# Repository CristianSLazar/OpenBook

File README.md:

# Hardware Functionality

The OpenBook E-Reader is designed with a focus on simplicity, sustainability, and open-source flexibility. Below is a detailed breakdown of its hardware components, interfaces, communication specifications, processes, and power consumption considerations.

## Block Diagram

## Bill of Materials

| Qty | Value | Device | Package | Parts | PURCHASE-URL | DATASHEET-URL |
| --- | ----- | ------ | ------- | ----- | ------------ | ------------- |
| 1 |  | ADAFRUIT_LEDCHIP-LED0603 | 0603 | CHG_LED | https://www.digikey.com/en/products/detail/w%C3%BCrth-elektronik/150060RS75000/4489901 | https://www.we-online.com/components/products/datasheet/150060RS75000.pdf |
| 1 | 0.1uF/50V | ESP32_WROVER_EAGLE-LTSPICE_C0402 | 0402 | EPD_C3 | https://www.digikey.com/en/products/detail/samsung-electro-mechanics/CL05B104KB5NNNC/11696318 | https://weblib.samsungsem.com/mlcc/mlcc-ec-data-sheet.do?partNumber=CL05B104KB5NNN |
| 1 | 0.47 | ESP32_WROVER_EAGLE-LTSPICE_RR0402 | 0402 | R3 | https://www.digikey.com/en/products/detail/panasonic-electronic-components/ERJ-2BQJR47X/5647384 | https://industrial.panasonic.com/cdbs/www-data/pdf/RDN0000/AOA0000C313.pdf |
| 1 | 100K | ESP32_WROVER_EAGLE-LTSPICE_RR0402 | 0402 | R_PWRUSB | https://www.digikey.com/en/products/detail/panasonic-electronic-components/ERJ-2RKF1003X/192081 | https://industrial.panasonic.com/cdbs/www-data/pdf/RDA0000/AOA0000C304.pdf |
| 8 | 100nF | ESP32_WROVER_EAGLE-LTSPICE_C0402 | 0402 | C1, C2, C3_USB, C5, C7, C8, C9, C_DELAY | https://www.digikey.com/en/products/detail/samsung-electro-mechanics/CL05B104KP5NNNC/3886660 | https://mm.digikey.com/Volume0/opasdata/d220001/medias/docus/609/CL05B104KP5NNNC_Spec.pdf |
| 1 | 100uF | RCL_CPOL-EUCT3528 | 3528 | C_TANT | https://ro.mouser.com/ProductDetail/KEMET/T491B107M006AT?qs=U312oeP%2FpiHOgyk6KO2m0g%3D%3D | https://ro.mouser.com/datasheet/2/447/KEM_T2005_T491-3316937.pdf
| 16 | 10K | ESP32_WROVER_EAGLE-LTSPICE_RR0402 | 0402 | R1, R1_PINH1, R1_PINH2, R2-PINH1, R2_PINH2, R4, R5, R6, R7, R8, R9, R10, R_BOOT, R_CHANGE, R_CL1, R_RESET | https://www.digikey.com/en/products/detail/panasonic-electronic-components/ERJ-2RKF1002X/192073 | https://industrial.panasonic.com/cdbs/www-data/pdf/RDA0000/AOA0000C304.pdf |
| 1 | 10uF | ESP32_WROVER_EAGLE-LTSPICE_C0402 | 0402 | C6 | https://www.digikey.com/en/products/detail/samsung-electro-mechanics/CL05A106MP5NUNC/3887108 | https://mm.digikey.com/Volume0/opasdata/d220001/medias/docus/2614/CL05A106MP5NUNC_Spec.pdf |
| 1 | 112A-TAAR-R03_ATTEND | 112A-TAAR-R03_ATTEND |  | J4 | https://www.digikey.ro/en/products/detail/attend-technology/112A-TAAR-R03/17633923 | https://www.attend.com.tw/data/download/file/112A-TAAR-R03_Spec.pdf |
| 1 | 15 | ESP32_WROVER_EAGLE-LTSPICE_RR0402 | 0402 | R_CAPACITOR | https://www.digikey.com/en/products/detail/panasonic-electronic-components/ERJ-2RKF15R0X/192142 | https://industrial.panasonic.com/cdbs/www-data/pdf/RDA0000/AOA0000C304.pdf |
| 1 | 1uF | ESP32_WROVER_EAGLE-LTSPICE_C0402 | 0402 | C4 | https://www.digikey.com/en/products/detail/samsung-electro-mechanics/CL05A105KO5NNNC/3886725 | https://mm.digikey.com/Volume0/opasdata/d220001/medias/docus/609/CL05A105KO5NNNC_Spec_5-2-19.pdf |
| 9 | 1uF/50V | ESP32_WROVER_EAGLE-LTSPICE_C0402 | 0402 | EPD_C1, EPD_C2, EPD_C4, EPD_C5, EPD_C6, EPD_C7, EPD_C8, EPD_C9, EPD_C10 | https://www.digikey.com/en/products/detail/murata-electronics/GRM155R61H105KE05D/13531808 | https://search.murata.co.jp/Ceramy/image/img/A01X/G101/ENG/GRM155R61H105KE05-01A.pdf |
| 1 | 2.2 | ESP32_WROVER_EAGLE-LTSPICE_RR0402 | 0402 | R2 | https://www.digikey.com/en/products/detail/panasonic-electronic-components/ERJ-2GEJ2R2X/282078 | https://api.pim.na.industrial.panasonic.com/file_stream/main/fileversion/1242 |
| 1 | 200 | ESP32_WROVER_EAGLE-LTSPICE_RR0402 | 0402 | R1_BAT | https://www.digikey.com/en/products/detail/panasonic-electronic-components/ERJ-2RKF2000X/192215 | https://industrial.panasonic.com/cdbs/www-data/pdf/RDA0000/AOA0000C304.pdf |
| 2 | 20V/4.2A/52mO/1.4W | ESP32_WROVER_SPARKFUN-DISCRETESEMI_MOSFET_PCH-DMG2305UX-7 |  | Q1, Q2 | https://www.digikey.ro/en/products/detail/diodes-incorporated/DMG2305UX-7/4340667 | https://www.diodes.com/assets/Datasheets/DMG2305UX.pdf |
| 1 | 2K | ESP32_WROVER_EAGLE-LTSPICE_RR0402 | 0402 | R2_BAT | https://www.digikey.com/en/products/detail/panasonic-electronic-components/ERJ-2RKF2001X/192194 | https://industrial.panasonic.com/cdbs/www-data/pdf/RDA0000/AOA0000C304.pdf |
| 5 | 4.7uF | ESP32_WROVER_EAGLE-LTSPICE_C0402 | 0402 | C1_BAT, C1_BAT1, C2_BAT, C2_BAT1, C4_USB | https://www.digikey.com/en/products/detail/samsung-electro-mechanics/CL05A475KQ5NRNC/3887139 | https://mm.digikey.com/Volume0/opasdata/d220001/medias/docus/41/CL05A475KQ5NRNC_Spec.pdf |
| 1 | 4.7uF/25V | ESP32_WROVER_EAGLE-LTSPICE_C0402 | 0402 | C3 | https://www.digikey.com/en/products/detail/murata-electronics/GRM155C61E475ME15D/16821133 | https://search.murata.co.jp/Ceramy/image/img/A01X/G101/ENG/GRM155C61E475ME15-01A.pdf |
| 2 | 5k1 | ESP32_WROVER_EAGLE-LTSPICE_RR0402 | 0402 | R1_USB, R2_USB | https://www.digikey.com/en/products/detail/panasonic-electronic-components/ERJ-2GEJ512X/147044 | https://api.pim.na.industrial.panasonic.com/file_stream/main/fileversion/1242 |
| 1 | 68uH | 744043680IND_4828-WE-TPC_WRE |  | L1 | https://www.digikey.de/en/products/detail/w%C3%BCrth-elektronik/744043680/1638515?srsltid=AfmBOoreM6iTR1zfidcAYx5855uFKN_t-1dK5Y4hJLHk64FUsesZV3qH | https://www.we-online.com/components/products/datasheet/744043680.pdf |
| 1 | BD5229G-TR | BD5229G-TR |  | U6 | https://www.digikey.com/en/products/detail/rohm-semiconductor/BD5229G-TR/658502 | https://www.rohm.com/datasheet?p=BD5229G&dist=Digi-key&media=referral&source=digi-key.com&campaign=Digi-key |
| 1 | BME688 | ESP32_WROVER_BME680_BME680 |  | U8 | https://www.digikey.ro/en/products/detail/bosch-sensortec/BME688/13681261 | https://www.bosch-sensortec.com/media/boschsensortec/downloads/datasheets/bst-bme688-ds000.pdf |
| 3 | BUTTON_CUSTOMV1 | BUTTON_CUSTOMV1 |  | BOOT_BUTTON, CHANGE_BUTTON, RESET_BUTTON |  |  |
| 1 | CPH3225A | CPH3225A |  | C_SUPERCAP | https://www.digikey.com/en/products/detail/seiko-instruments/CPH3225A/8692444 | https://mm.digikey.com/Volume0/opasdata/d220001/medias/docus/6537/rev05-CPHCPM.pdf |
| 1 | DS3231SN# | DS3231SN# |  | U3 | https://www.digikey.com/en/products/detail/analog-devices-inc-maxim-integrated/DS3231SN/1197576 | https://www.analog.com/media/en/technical-documentation/data-sheets/DS3231.pdf |
| 1 | ESP32-C6-WROOM-1-N8 | ESP32-C6-WROOM-1-N8 |  | U1 | https://www.digikey.com/en/products/detail/espressif-systems/ESP32-C6-WROOM-1-N8/17728866 | https://www.espressif.com/sites/default/files/documentation/esp32-c6-wroom-1_wroom-1u_datasheet_en.pdf |
| 1 | ESP32C6_VARISTORCN1812 | ESP32C6_VARISTORCN1812 |  | PFMF.050.1 | https://www.digikey.com/en/products/detail/schurter-inc/PFMF-050-2/1731348 | https://us.schurter.com/en/datasheet/typ_PFMF.pdf |
| 2 | ESP32_WROVER_AVX---SD0805S020S1R0 | ESP32_WROVER_AVX---SD0805S020S1R0 |  | D2, D7 | https://www.digikey.gr/en/products/detail/kyocera-avx/SD0805S020S1R0/3749517 | https://datasheets.kyocera-avx.com/schottky.pdf |
| 1 | FH34SRJ-24S-0.5SH_99_ | FH34SRJ-24S-0.5SH_99_ |  | J1 | https://www.digikey.com/en/products/detail/hirose-electric-co-ltd/FH34SRJ-24S-0-5SH-99/5132529 | https://www.hirose.com/en/product/document?clcode=CL0580-1253-0-99&productname=FH34SRJ-12S-0.5SH(99)&series=FH34SRJ&documenttype=SpecSheet&lang=en&documentid=0000414526 |
| 1 | MAX17048G+T10 | MAX17048G+T10 |  | U2 | https://www.digikey.com/en/products/detail/analog-devices-inc-maxim-integrated/MAX17048G-T10/3758921 | https://datasheets.maximintegrated.com/en/ds/MAX17048-MAX17049.pdf |
| 3 | MBR0530 | MBR0530 |  | D3, D4, D5 | https://eu.mouser.com/ProductDetail/Micro-Commercial-Components-MCC/MBR0530-TP?qs=KFo7JewZbUECRHkxGanrdg%3D%3D&srsltid=AfmBOopI5EY-Qmh6fu8QJtXckZ14Imu1WB2G5-0En3D3mZ6aqi4jmsQ2 | https://eu.mouser.com/datasheet/2/258/MBR0520_MBR0580_SOD123_-2492194.pdf |
| 1 | MCP73831 | ESP32_WROVER_SPARKFUN-IC-POWER_MCP73831 |  | U7 | https://www.digikey.com/en/products/detail/microchip-technology/MCP73831T-2ACI-OT/964301 | https://ww1.microchip.com/downloads/en/DeviceDoc/MCP73831-Family-Data-Sheet-DS20001984H.pdf |
| 6 | PGB1010603MR | PGB1010603MR |  | D6, D8, D9, D10, D11, D12 | https://www.digikey.com/en/products/detail/littelfuse-inc/PGB1010603MR/715755 | https://www.littelfuse.com/assetdocs/pulseguard-esd-suppressors-pgb1-datasheet?assetguid=8a337998-d54d-466b-be4e-dc5bcd1f9321 |
| 1 | QWIIC_RIGHT_ANGLE | QWIIC_CONNECTORJS-1MM |  | J3 | https://www.sparkfun.com/qwiic-jst-connector-smd-4-pin-horizontal.html | https://cdn.sparkfun.com/assets/parts/1/2/2/8/9/Qwiic_Connector_Datasheet.pdf |
| 1 | SAMACSYS_PARTS_USB4110-GF-A | SAMACSYS_PARTS_USB4110-GF-A |  | J2 | https://www.digikey.ro/en/products/detail/gct/USB4110-GF-A/10384547 | https://gct.co/files/specs/usb4110-spec.pdf?v=6b2a6292-70a5-4bd5-a7e5-0f3fe03e015f |
| 1 | SI1308EDL-T1-GE3 | SI1308EDL-T1-GE3 |  | Q3 | https://www.digikey.com/en/products/detail/vishay-siliconix/SI1308EDL-T1-GE3/4876435 | https://www.vishay.com/docs/63399/si1308edl.pdf |
| 1 | USBLC6-2SC6Y | USBLC6-2SC6Y |  | D1 | https://www.digikey.com/en/products/detail/stmicroelectronics/USBLC6-2SC6Y/2819177 | https://www.st.com/content/ccc/resource/technical/document/datasheet/group0/94/15/6c/58/ba/91/46/42/DM00055262/files/DM00055262.pdf/jcr:content/translations/en.DM00055262.pdf |
| 1 | W25Q512JVEIQ | W25Q512JVEIQ |  | U4 | https://www.digikey.com/en/products/detail/winbond-electronics/W25Q512JVEIQ/10244706 | https://www.winbond.com/resource-files/W25Q512JV%20SPI%20RevB%2006252019%20KMS.pdf |
| 1 | XC6220A331MR-G | XC6220A331MR-G |  | U5 | https://www.digikey.in/en/products/detail/torex-semiconductor-ltd/XC6220A331MR-G/10165775 | https://product.torexsemi.com/system/files/series/xc6220.pdf |
| 1 | | CELLEVIA BATTERIES LP584174 | | https://www.tme.eu/en/details/accu-lp584174_cl/rechargeable-batteries/cellevia-batteries/l584174/ | https://www.tme.eu/Document/e0683d8c34e6d878124489f71bffb6ee/cel0014.pdf
| 1 | | Waveshare 7.5inch e-Paper V2 | | https://www.waveshare.com/7.5inch-e-paper-hat.htm | https://files.waveshare.com/upload/6/60/7.5inch_e-Paper_V2_Specification.pdf
| 1 | | Casing | | | |

## Core Hardware Components

1. **Microcontroller**

    * Model: ESP32-C6-WROOM-1 (or equivalent) for its integrated Wi-Fi 6, BLE 5, and ample processing power.

    * Functionality: Manages display rendering, input handling, sensor data processing, and communication.

    * Interfaces: Communicates with peripherals via SPI, I²C, UART, and GPIO.

2. **Display**

    * Model: Waveshare WSH-13187 7.5inch e-Paper display.

    * Resolution: 800x480.

    * Interface: SPI (Serial Peripheral Interface).

    * Functionality:

        * Provides a paper-like reading experience.

        * Only consumes power when changing content.

3. **Sensors (for environmental monitoring)**

    * Interface: All sensors communicate via I²C bus (reduces pin usage).

    * Process: Sensor readings are periodically captured and displayed for user awareness.

    | Sensor Type | Function | Model | Interface | Power Consumption |
    | ----------- | -------- | ------------ | --------- | ----------------- |
    | Temperature | Measures ambient temperature | Bosch BME688 | I²C | ~1.8mA @ 3.3V |
    | Humidity | Measures relative humidity | Bosch BME688 | I²C | ~1.8mA @ 3.3V |
    | Pressure | Measures atmospheric pressure | Bosch BMP288 | I²C | ~2.7mA @ 3.3V |
    | Air Quality | Estimates VOC and pollution levels | Bosch BME688 | I²C | ~12mA @ 3.3V |

4. **Buttons & User Interface**

    * Buttons: Three physical buttons for page navigation and menu control.

    * Interface: GPIO (General Purpose Input/Output).

    * Functionality:

        * Provides a tactile, distraction-free experience.

        * Reduces reliance on touchscreen power consumption.

5. **Connectivity**

    * Wi-Fi Module: Integrated in MCU.

        * Interface: SPI or UART.

        * Functionality: Enables e-book downloads, firmware updates, and online features.

    * USB-C Port:

        * Functions:

            * Charging (5V/1A).

            * Data transfer for sideloading books.

        * Interface: USB 2.0.

6. **Storage**

    * SD Memory Card Connector: Attend Tech 112A-TAAR-R03.

        * Interface: SPI.

    * External Flash: MAX17048G.

        * Interface: SPI.

    * Functionality: Stores books, firmware, and settings.

7. **Power System**

    * Battery: 2500mAh Lithium-Polymer battery.

    * Charging Interface: USB-C, 5V/1A.

    * Battery Management:

        * Uses MCP73831 Power Management IC.

        * Includes overcharge, over-discharge, and short-circuit protection.

    * Expected Battery Life: At least one week per charge.

## Communication and Data Flow

### Communication Interfaces

| Component | Interface | Function |
| --------- | ---------| -------- |
| Microcontroller - Display | SPI | Transfers image data to the e-paper screen |
| Microcontroller - Sensors | I²C | Reads environmental sensor data |
| Microcontroller - Storage | SPI | Reads/writes e-books and firmware |
| Microcontroller - USB-C | USB 2.0 | Data transfer & charging |

## Power Consumption Estimation

| Component | Active Power (mW) | Sleep Power (mW) | Notes |
| --------- | ----------------- | ---------------- | ----- |
| Microcontroller | 50–150mW | 10mW | Depends on task |
| E-Paper Display | ~500mW (refresh) | ~0mW | Only consumes power during refresh |
| Wi-Fi Module | ~250mW | ~5mW | Wi-Fi off in sleep mode |
| Temperature Sensor | 1.8mW | 0.1mW | I²C bus shared |
| Humidity Sensor | 1.8mW | 0.1mW | I²C bus shared |
| Pressure Sensor | 2.7mW | 0.1mW | I²C bus shared |
| Air Quality Sensor | 12mW | 1mW | Runs periodic checks |
| Physical Buttons | 0mW | 0mW | Uses GPIO interrupts |
| USB-C Charging | ~5W | - | Only active when charging |

### Estimated Battery Life

**Average Power Consumption**: ~200mW (normal reading mode).

**Battery Capacity**: ~2500mAh (~9.25Wh @ 3.7V).

**Runtime Calculation**:

* 9.25Wh0.2W≈46 hours of active reading
* 0.2W9.25Wh​≈46 hours of active reading

This translates to 1–2 weeks per charge, assuming ~3–4 hours of daily reading.

## Additional Considerations

* Regulatory Compliance:

    FCC (wireless compliance), CE (safety), RoHS (environmental standards).

* Thermal Design:

    Passive cooling (no fans required due to low power usage).

* Firmware Update Process:

    * OTA (Over-the-Air) updates via Wi-Fi.

    * USB sideloading as a fallback.

* Modular Expansion Possibilities:

    * Future support for Bluetooth (e.g., syncing annotations).

    * Open GPIO pins for DIY modifications.

## Microcontroller Pin Assignments

### SPI (Serial Peripheral Interface) – For Display and Storage

SPI is used for fast data transmission between the MCU and E-paper display and Flash storage.

| Component | Signal Name | Pin Number | Description |
| --------- | ------------ | ---------- | ----------- |
| E-Paper Display | MOSI | GPIO 7 | Master Out, transmits image data |
| | MISO | GPIO 2 | Master In, not used (one-way communication) |
| | SCK | GPIO 6 | Clock signal for SPI |
| | EPD_CS | GPIO 10 | Chip Select for E-paper display |
| | EPD_BUSY | GPIO 3 | Display busy signal (high = busy) |
| | EPD_RST | GPIO 23 | Hardware reset for the display |
| | EDP_DC | GPIO 5 | Serial communication Data/Command input
| SD Card |	MOSI | GPIO 7 | Shared MOSI pin |
| | MISO | GPIO 2 | Shared MISO pin |
| | SCK | GPIO 6 | Shared Clock pin |
| | SS_SD | GPIO 16 | Chip Select for SD Card |
| External Flash | MOSI | GPIO 7 | Shared MOSI pin |
| | MISO | GPIO 2 | Shared MISO pin |
| | SCK | GPIO 6 | Shared Clock pin |
| | FLASH_CS | GPIO 11 | Chip Select for external flash |

**Note**: The same SPI bus is shared between the e-paper display and storage, but they have separate chip select (CS) lines.

## I²C (Inter-Integrated Circuit) - For Sensors

I²C is used for low-power, two-wire communication with environmental sensors.

| Component | Signal Name | Pin Number | Description |
| --------- | ------------ | ---------- | ----------- |
| Environmental Sensor | SDA | GPIO 21 | Data line |
| | SCL | GPIO 22 | Clock line |

**Note**: All sensors share the same I²C bus (SDA & SCL), differentiated by unique I²C addresses.

### UART (Universal Asynchronous Receiver-Transmitter) – For Communication Modules

UART is used for serial debugging.

| Signal Name | Pin Number | Description |
| ------------ | ---------- | ----------- |
| TX | GPIO 16 | Debug TX output |
| RX | GPIO 17 | Debug RX input |

### GPIO (General Purpose Input/Output) – For Buttons & LEDs

GPIO pins are used for physical buttons, status LEDs, and interrupts.

| Component | Signal Name | Pin Number | Description |
| --------- | ----------- | ---------- | ----------- |
| I/O (Boot) Button | IO/BOOT | GPIO 9 | Button press input |
| Reset Button | RESET | EN | Button press input |
| I/O (Change) Button | IO/CHANGE | GPIO 15 | Button press input |

### RTC pins

| Component | Signal Name | Pin Number | Description |
| --------- | ----------- | ---------- | ----------- |
| Real Time Clock | INT_RTC | GPIO 0 | Interrupt line |
| | RTC_RST | GPIO 18 | Clock reset line |
| | 32KHZ | GPIO 1| Clock line |

### USB data pins

| Component | Signal Name | Pin Number | Description |
| --------- | ----------- | ---------- | ----------- |
| USB Connector | USB_D+ | GPIO 13 | Positive differential data line |
| USB Connector | USB_D- | GPIO 12 | Negative differential data line |

## Conclusion

The OpenBook E-Reader is a well-optimized, low-power device that leverages an efficient microcontroller, e-paper display, and integrated environmental sensors. By utilizing SPI, I²C, and GPIO interfaces, it ensures a simple yet powerful design with extended battery life, modularity, and open-source flexibility. The estimated power consumption aligns well with the goal of at least one week of reading per charge, making it a compelling alternative to mainstream e-readers.

## Notes

* Content of README.md adapted from generated response by ChatGPT
* Power consumption estimations and calculations generated by ChatGPT

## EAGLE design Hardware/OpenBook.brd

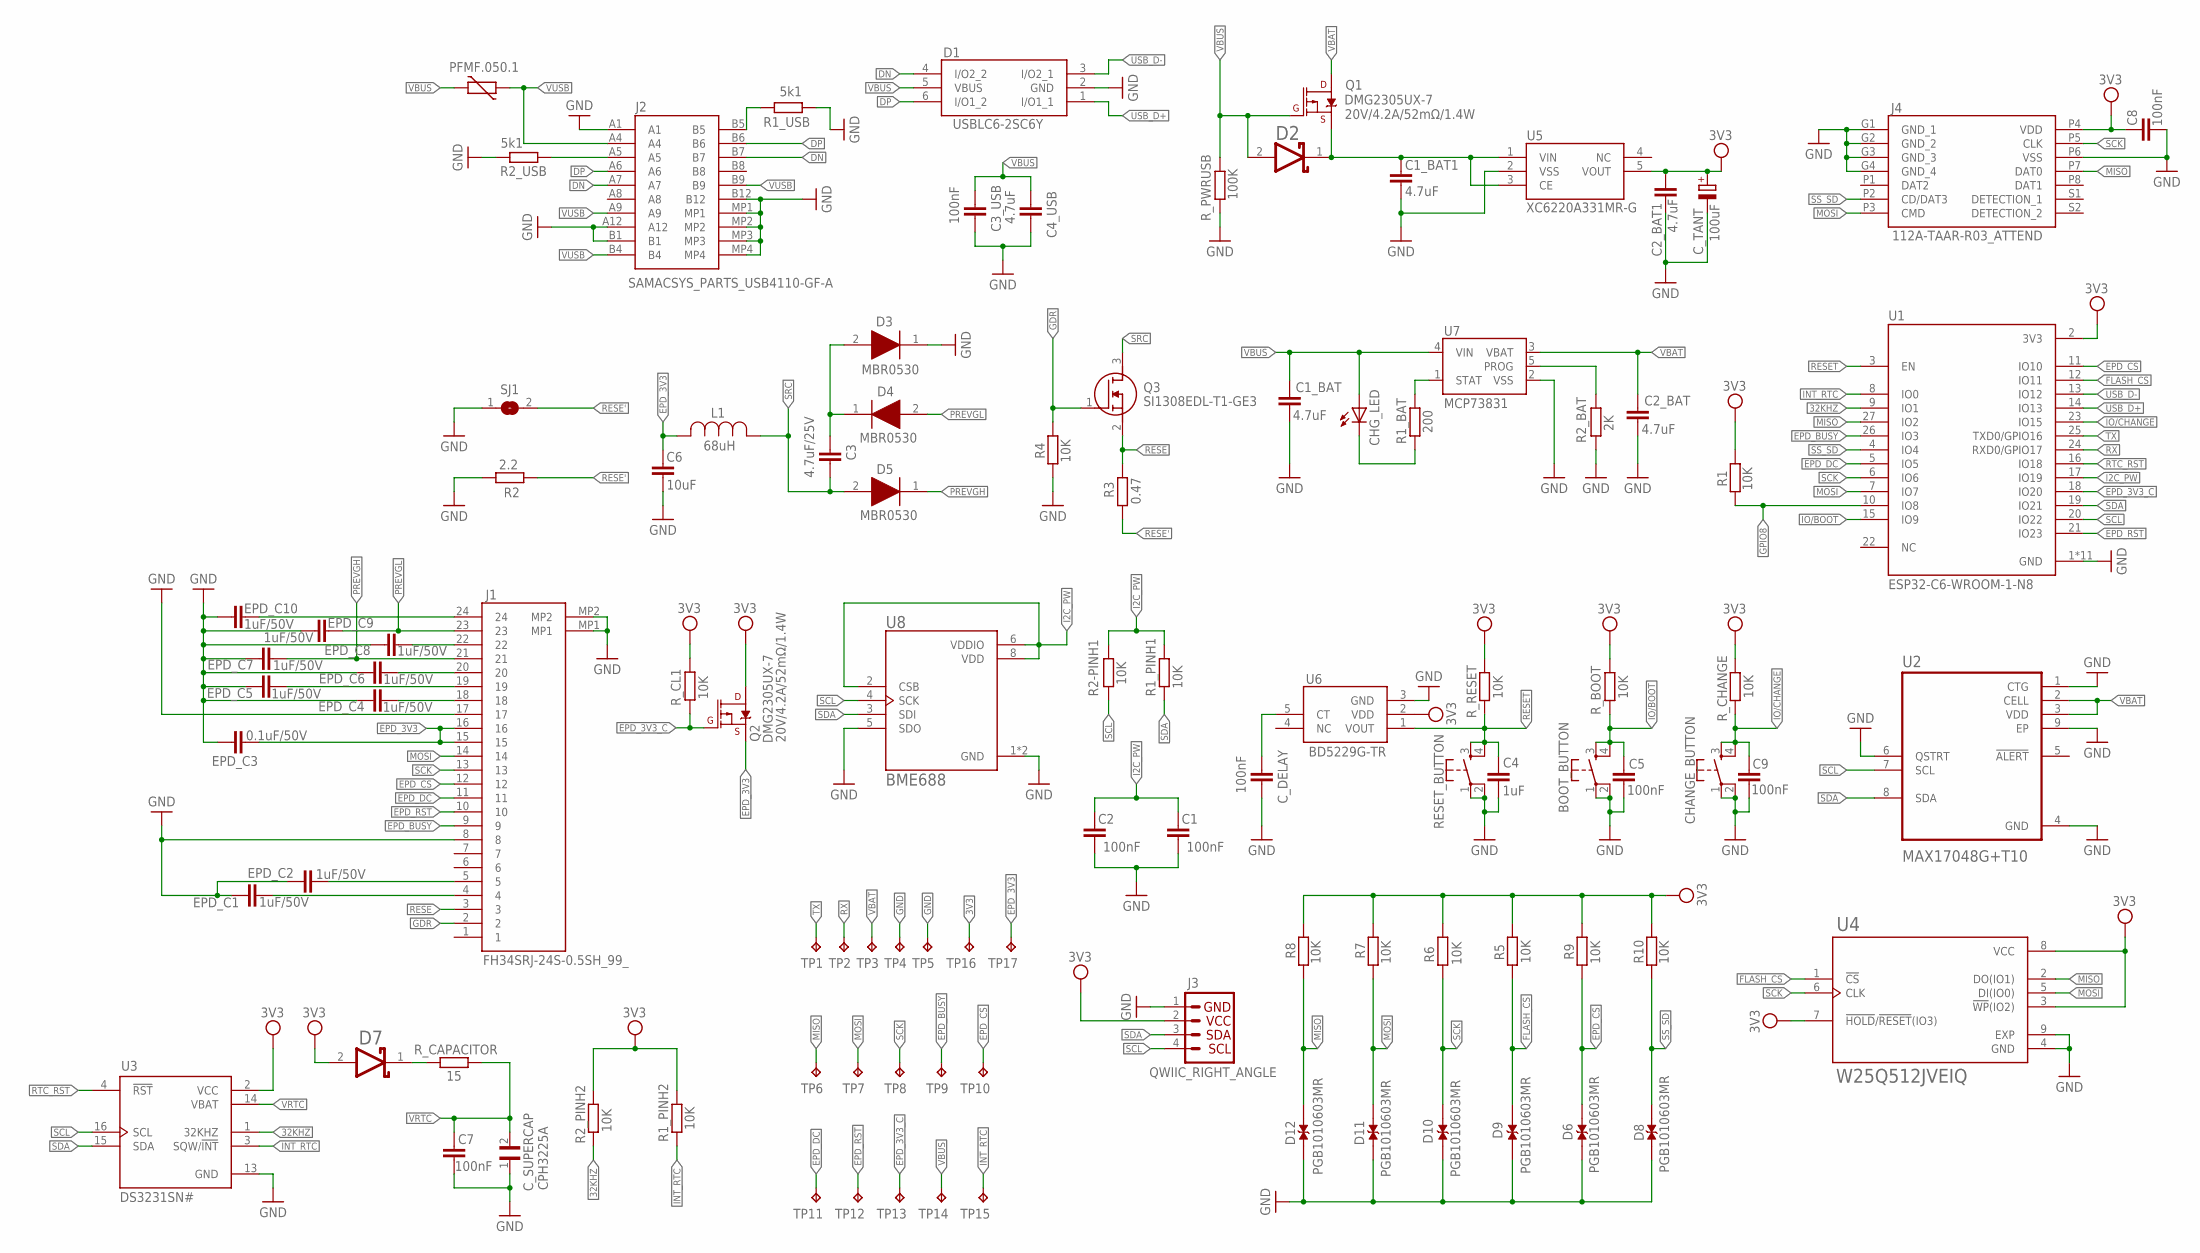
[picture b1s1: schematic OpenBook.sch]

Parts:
BOOT_BUTTON: BUTTON_CUSYOMV1; MYBUTTON
C1, C2, C3_USB, C5, C7, C8, C9: 100nF; EAGLE-LTSPICE_C0402
C1_BAT, C1_BAT1, C2_BAT, C2_BAT1, C4_USB: 4.7uF; EAGLE-LTSPICE_C0402
C3: 4.7uF/25V; EAGLE-LTSPICE_C0402
C4: 1uF; EAGLE-LTSPICE_C0402
C6: 10uF; EAGLE-LTSPICE_C0402
CHANGE_BUTTON: BUTTON_CUSYOMV1; MYBUTTON
CHG_LED: ADAFRUIT_LEDCHIP-LED0603; ADAFRUIT_CHIP-LED0603
C_DELAY: 100nF; EAGLE-LTSPICE_C0402
C_SUPERCAP: CPH3225A; CAPCP3225X100N
C_TANT: 100uF; RCL_CT3528
D1: USBLC6-2SC6Y; SON50P200X200X80-9N
D2, D7: ESP32_WROVER_AVX---SD0805S020S1R0_AVX_SD0805S020S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; ESP32_WROVER_AVX---SD0805S020S1R0_AVX_SD0805S020S1R0_0
D3, D4, D5: MBR0530; SOD3716X135N
D6, D8, D9, D10, D11, D12: PGB1010603MR; DIOC1608X36N
EPD_C1, EPD_C2, EPD_C4, EPD_C5, EPD_C6, EPD_C7, EPD_C8, EPD_C9, EPD_C10: 1uF/50V; EAGLE-LTSPICE_C0402
EPD_C3: 0.1uF/50V; EAGLE-LTSPICE_C0402
J1: FH34SRJ-24S-0.5SH_99_; FH34SRJ24S05SH99
J2: SAMACSYS_PARTS_USB4110-GF-A; SAMACSYS_PARTS_USB4110GFA
J3: QWIIC_RIGHT_ANGLE; JST04_1MM_RA
J4: 112A-TAAR-R03_ATTEND; 112ATAARR03ATTEND
L1: 68uH; IND_4828-WE-TPC_WRE
PFMF.050.1: ESP32C6_VARISTORCN1812; ESP32C6_VARISTOR_CT/CN1812
Q1, Q2: 20V/4.2A/52mΩ/1.4W; ESP32_WROVER_SPARKFUN-DISCRETESEMI_SOT23-3
Q3: SI1308EDL-T1-GE3; SOT65P210X110-3N
R1, R1_PINH1, R1_PINH2, R2-PINH1, R2_PINH2, R4, R5, R6, R7, R8, R9, R10: 10K; ESP32_WROVER_EAGLE-LTSPICE_R0402
R1_BAT: 200; ESP32_WROVER_EAGLE-LTSPICE_R0402
R1_USB, R2_USB: 5k1; ESP32_WROVER_EAGLE-LTSPICE_R0402
R2: 2.2; ESP32_WROVER_EAGLE-LTSPICE_R0402
R2_BAT: 2K; ESP32_WROVER_EAGLE-LTSPICE_R0402
R3: 0.47; ESP32_WROVER_EAGLE-LTSPICE_R0402
RESET_BUTTON: BUTTON_CUSYOMV1; MYBUTTON
R_BOOT: 10K; ESP32_WROVER_EAGLE-LTSPICE_R0402
R_CAPACITOR: 15; ESP32_WROVER_EAGLE-LTSPICE_R0402
R_CHANGE: 10K; ESP32_WROVER_EAGLE-LTSPICE_R0402
R_CL1: 10K; ESP32_WROVER_EAGLE-LTSPICE_R0402
R_PWRUSB: 100K; ESP32_WROVER_EAGLE-LTSPICE_R0402
R_RESET: 10K; ESP32_WROVER_EAGLE-LTSPICE_R0402
SJ1: SJ
TP1, TP2, TP3, TP4, TP5, TP6, TP7, TP8, TP9, TP10, TP11, TP12, TP13, TP14, TP15, TP16, TP17: TPTP20R; TP20R
U1: ESP32-C6-WROOM-1-N8; XCVR_ESP32-C6-WROOM-1-N8
U2: MAX17048G+T10; SON50P200X200X80-9N
U3: DS3231SN#; SOIC127P1032X265-16N
U4: W25Q512JVEIQ; SON127P600X800X80-9N
U5: XC6220A331MR-G; SOT95P280X120-5N
U6: BD5229G-TR; SOT95P280X125-5N
U7: MCP73831; ESP32_WROVER_SPARKFUN-IC-POWER_SOT23-5
U8: BME688; ESP32_WROVER_BME680_PSON80P300X300X100-8N

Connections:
3V3: C2_BAT1.1, C8.1, C_TANT.+, D7.2 (ANODE), J3.2, J4.P4 (VDD), Q2.3 (D), R1.2, R1_PINH2.2, R2_PINH2.2, R5.2, R6.2, R7.2, R8.2, R9.2, R10.2, R_BOOT.2, R_CHANGE.2, R_CL1.2, R_RESET.2, TP16.TP, U1.2 (3V3), U3.2 (VCC), U4.3 (!WP!(IO2)), U4.7 (!HOLD!/!RESET!(IO3)), U4.8 (VCC), U5.5 (VOUT), U6.2 (VDD)
32KHZ: R2_PINH2.1, U1.9 (IO1), U3.1 (32KHZ)
DN: D1.4 (I/O2_2), J2.A7, J2.B7
DP: D1.6 (I/O1_2), J2.A6, J2.B6
EPD_3V3: C6.1, EPD_C3.2, J1.15, J1.16, L1.2, Q2.2 (S), TP17.TP
EPD_3V3_C: Q2.1 (G), R_CL1.1, TP13.TP, U1.18 (IO20)
EPD_BUSY: J1.9, TP9.TP, U1.26 (IO3)
EPD_CS: D6.2, J1.12, R9.1, TP10.TP, U1.11 (IO10)
EPD_DC: J1.11, TP11.TP, U1.5 (IO5)
EPD_RST: J1.10, TP12.TP, U1.21 (IO23)
FLASH_CS: D9.2, R5.1, U1.12 (IO11), U4.1 (!CS)
GDR: J1.2, Q3.1 (G), R4.2
GND: BOOT_BUTTON.1, BOOT_BUTTON.2, C1.2, C1_BAT.2, C1_BAT1.2, C2.2, C2_BAT.2, C2_BAT1.2, C3_USB.2, C4.2, C4_USB.2, C5.2, C6.2, C7.2, C8.2, C9.2, CHANGE_BUTTON.1, CHANGE_BUTTON.2, C_DELAY.2, C_SUPERCAP.1, C_TANT.-, D1.2 (GND), D3.1 (K), D6.1, D8.1, D9.1, D10.1, D11.1, D12.1, EPD_C1.1, EPD_C2.1, EPD_C3.1, EPD_C4.1, EPD_C5.1, EPD_C6.1, EPD_C7.1, EPD_C8.1, EPD_C9.1, EPD_C10.1, J1.8, J1.17, J1.MP1, J1.MP2, J2.A1, J2.A12, J2.B1, J2.B12, J2.MP1, J2.MP2, J2.MP3, J2.MP4, J3.1, J4.G1 (GND_1), J4.G2 (GND_2), J4.G3 (GND_3), J4.G4 (GND_4), J4.P6 (VSS), R1_USB.2, R2.2, R2_BAT.1, R2_USB.1, R4.1, RESET_BUTTON.1, RESET_BUTTON.2, R_PWRUSB.1, SJ1.1, TP4.TP, TP5.TP, U1.1 (GND), U1.28 (GND), U1.29_1 (GND), U1.29_2 (GND), U1.29_3 (GND), U1.29_4 (GND), U1.29_5 (GND), U1.29_6 (GND), U1.29_7 (GND), U1.29_8 (GND), U1.29_9 (GND), U2.1 (CTG), U2.4 (GND), U2.6 (QSTRT), U2.9 (EP), U3.13 (GND), U4.4 (GND), U4.9 (EXP), U5.2 (VSS), U6.3 (GND), U7.2 (VSS), U8.1 (GND), U8.5 (SDO), U8.7 (GND)
GPIO8: R1.1, U1.10 (IO8)
I2C_PW: C1.1, C2.1, R1_PINH1.2, R2-PINH1.2, U1.17 (IO19), U8.2 (CSB), U8.6 (VDDIO), U8.8 (VDD)
INT_RTC: R1_PINH2.1, TP15.TP, U1.8 (IO0), U3.3 (SQW/!INT)
IO/BOOT: BOOT_BUTTON.3, BOOT_BUTTON.4, C5.1, R_BOOT.1, U1.15 (IO9)
IO/CHANGE: C9.1, CHANGE_BUTTON.3, CHANGE_BUTTON.4, R_CHANGE.1, U1.23 (IO15)
MISO: D12.2, J4.P7 (DAT0), R8.1, TP6.TP, U1.27 (IO2), U4.2 (DO(IO1))
MOSI: D11.2, J1.14, J4.P3 (CMD), R7.1, TP7.TP, U1.7 (IO7), U4.5 (DI(IO0))
unnamed: C1_BAT1.1, D2.1 (CATHODE), Q1.2 (S), U5.1 (VIN), U5.3 (CE)
unnamed: R1_BAT.2, U7.1 (STAT)
unnamed: C3.1, D3.2 (A), D4.1 (K)
unnamed: J2.A5, R2_USB.2
unnamed: CHG_LED.C, R1_BAT.1
unnamed: J2.B5, R1_USB.1
unnamed: C_DELAY.1, U6.5 (CT)
unnamed: EPD_C8.2, J1.22
unnamed: EPD_C6.2, J1.20
unnamed: EPD_C4.2, J1.18
unnamed: R2_BAT.2, U7.5 (PROG)
unnamed: EPD_C5.2, J1.19
unnamed: EPD_C10.2, J1.24
unnamed: D7.1 (CATHODE), R_CAPACITOR.1
unnamed: EPD_C2.2, J1.5
unnamed: EPD_C1.2, J1.4
PREVGH: D5.1 (K), EPD_C7.2, J1.21
PREVGL: D4.2 (A), EPD_C9.2, J1.23
RESE: J1.3, Q3.2 (S), R3.2
RESE': R2.1, R3.1, SJ1.2
RESET: C4.1, RESET_BUTTON.3, RESET_BUTTON.4, R_RESET.1, U1.3 (EN), U6.1 (VOUT)
RTC_RST: U1.16 (IO18), U3.4 (!RST)
RX: TP2.TP, U1.24 (RXD0/GPIO17)
SCK: D10.2, J1.13, J4.P5 (CLK), R6.1, TP8.TP, U1.6 (IO6), U4.6 (CLK)
SCL: J3.4, R2-PINH1.1, U1.20 (IO22), U2.7 (SCL), U3.16 (SCL), U8.4 (SCK)
SDA: J3.3, R1_PINH1.1, U1.19 (IO21), U2.8 (SDA), U3.15 (SDA), U8.3 (SDI)
SRC: C3.2, D5.2 (A), L1.1, Q3.3 (D)
SS_SD: D8.2, J4.P2 (CD/DAT3), R10.1, U1.4 (IO4)
TX: TP1.TP, U1.25 (TXD0/GPIO16)
USB_D+: D1.1 (I/O1_1), U1.14 (IO13)
USB_D-: D1.3 (I/O2_1), U1.13 (IO12)
VBAT: C2_BAT.1, Q1.3 (D), TP3.TP, U2.2 (CELL), U2.3 (VDD), U7.3 (VBAT)
VBUS: C1_BAT.1, C3_USB.1, C4_USB.1, CHG_LED.A, D1.5 (VBUS), D2.2 (ANODE), PFMF.050.1.2, Q1.1 (G), R_PWRUSB.2, TP14.TP, U7.4 (VIN)
VRTC: C7.1, C_SUPERCAP.2, R_CAPACITOR.2, U3.14 (VBAT)
VUSB: J2.A4, J2.A9, J2.B4, J2.B9, PFMF.050.1.1

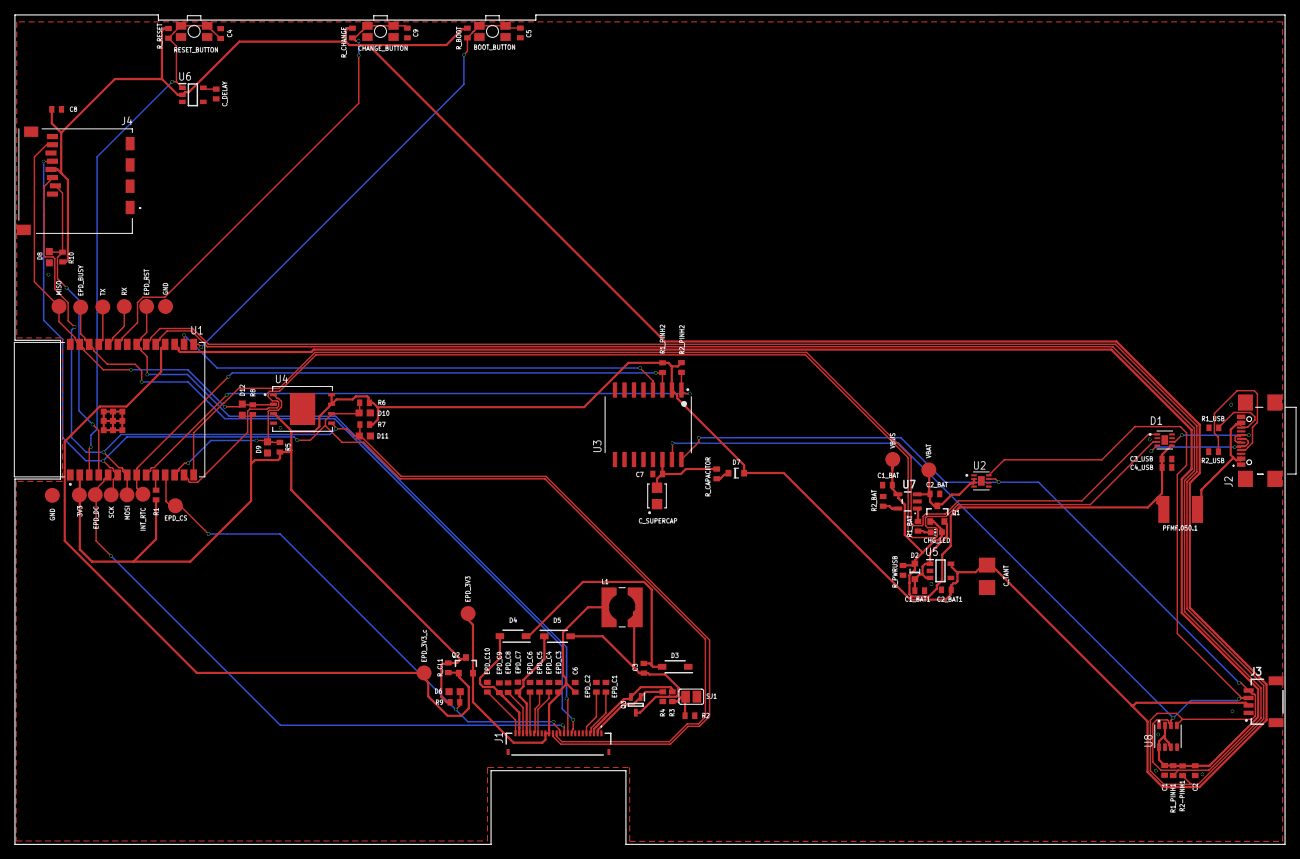
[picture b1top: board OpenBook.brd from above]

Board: 2 copper layers, 170.1 x 111.1 mm, 103 parts (0 on the bottom side), 55 nets.

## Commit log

2025-03-24 Added schematic
2025-04-05 Create LICENSE
2025-04-06 Added the project.
2025-04-06 Addead README.md
2025-04-12 Fixes #2, fixes #3; Adds the frame and module names in the schematic
2025-04-12 Fixes #6, fixes #7, fixes #9
2025-04-12 Modified PCB dielectric layer thickness
2025-04-14 Fixes #10; Fixes overlaps and misdimensions in 3d model and changes format of board and schematic files
2025-04-14 Update README.md
    Fixes #11; Adds missing components to README bill of materials
2025-04-15 Renames schematic
2025-04-15 Moves schematic separation lines to Info layer
2025-04-15 Hides sketches in 3d model
2025-04-15 Updates images
